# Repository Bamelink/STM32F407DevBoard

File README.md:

# STM32F407DevBoard
A developer board created in kicad featuring a STM32F407 MCU, LAN and CAN

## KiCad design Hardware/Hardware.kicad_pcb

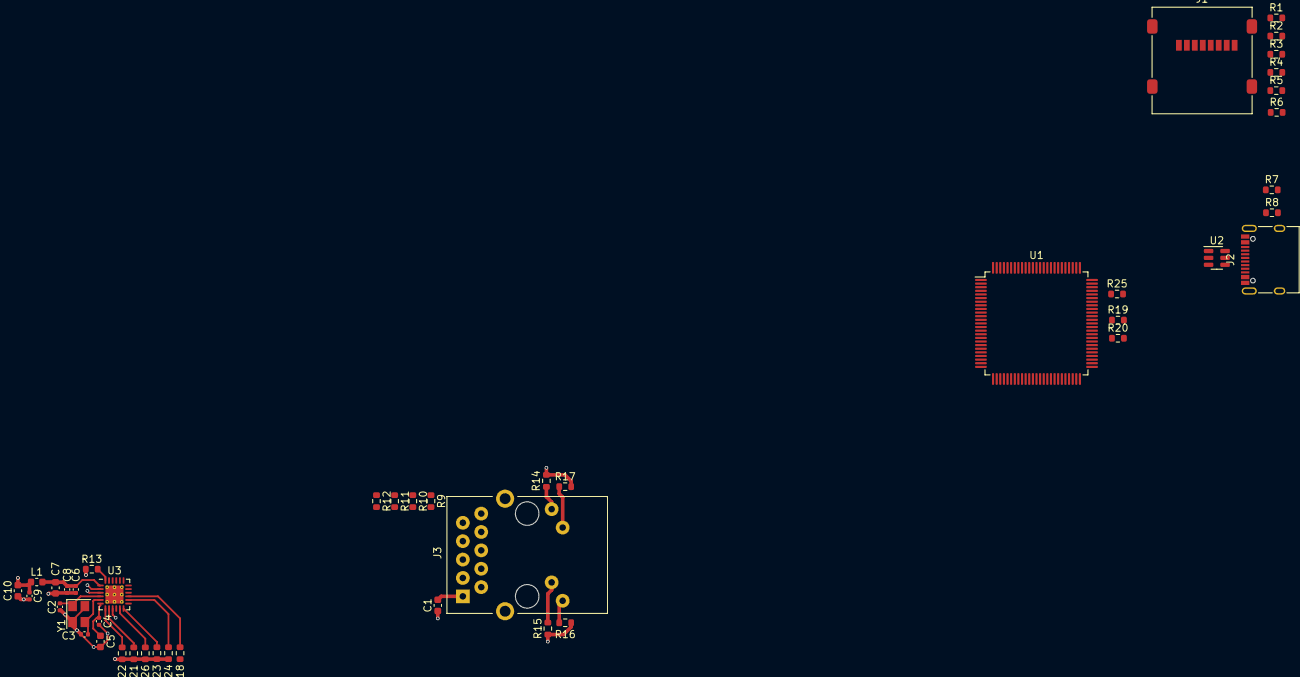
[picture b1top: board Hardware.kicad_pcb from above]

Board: 4 copper layers, 44 parts (0 on the bottom side), 41 nets.

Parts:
C1: TBD; C_0603_1608Metric
C2, C3: TBD; C_0402_1005Metric
C4: 470p; C_0402_1005Metric
C5: 1u; C_0603_1608Metric
C6, C8, C9: 100n; C_0402_1005Metric
C7, C10: 10u; C_0603_1608Metric
J1: Micro_SD_Card; microSD_HC_Molex_47219-2001
J2: USB_C_Receptacle_USB2.0; USB_C_Receptacle_XKB_U262-16XN-4BVC11
J3: RJ45_RB1-125B8G1A; RJ45_UDE_RB1-125B8G1A
L1: BLM18PG121SN1D; L_0603_1608Metric
R1, R2, R3, R4, R5, R6: 47k; R_0603_1608Metric
R7, R8: 5k1; R_0603_1608Metric
R9, R10, R11, R12: 50R; R_0603_1608Metric
R13: 12k1; R_0603_1608Metric
R14, R15: 10k; R_0603_1608Metric
R16, R17: 330R; R_0603_1608Metric
R18: 100k; R_0603_1608Metric
R19, R20, R25: 33R; R_0603_1608Metric
R21, R22, R24: 4k7; R_0603_1608Metric
R23, R26: 1k5; R_0603_1608Metric
U1: STM32F407VET6; LQFP-100_14x14mm_P0.5mm
U2: USBLC6-2SC6; SOT-23-6
U3: LAN8742A; VQFN-24-1EP_4x4mm_P0.5mm_EP2.5x2.5mm_ThermalVias
Y1: 25MHz; Crystal_SMD_3225-4Pin_3.2x2.5mm

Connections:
+3V3: C1.1, C9.1, C10.1, J1.4 (VDD), J3.R1 (CT), L1.2, R1.1, R2.1, R3.1, R4.1, R5.1, R6.1, R9.1, R10.1, R11.1, R12.1, R21.2, R22.1, R23.2, R24.1, R26.2, U1.6 (VBAT), U1.11 (VDD), U1.19 (VDD), U1.28 (VDD), U1.50 (VDD), U1.75 (VDD), U1.100 (VDD), U3.9 (VDDIO)
/IO/ETH_LED1: J3.L3, R15.1, U3.3 (LED1/REGOFF)
/IO/ETH_LED2: J3.L1, R14.1, U3.2 (LED2/~INTSEL)
/IO/ETH_RX+: J3.R4 (TD2+), R10.2, U3.23 (RXP)
/IO/ETH_RX-: J3.R5 (TD2-), R9.2, U3.22 (RXN)
/IO/ETH_TX+: J3.R2 (TD1+), R12.2, U3.21 (TXP)
/IO/ETH_TX-: J3.R3 (TD1-), R11.2, U3.20 (TXN)
/IO/SDIO_CK: J1.5 (CLK), R3.2, U1.80 (PC12)
/IO/SDIO_CMD: J1.3 (CMD), R4.2, U1.83 (PD2)
/IO/SDIO_D0: J1.7 (DAT0), R2.2, U1.65 (PC8)
/IO/SDIO_D1: J1.8 (DAT1), R1.2, U1.66 (PC9)
/IO/SDIO_D2: J1.1 (DAT2), R6.2, U1.78 (PC10)
/IO/SDIO_D3: J1.2 (DAT3/CD), R5.2, U1.79 (PC11)
/IO/USB_CC1: J2.A5 (CC1), R8.1
/IO/USB_CC2: J2.B5 (CC2), R7.1
/IO/USB_MCU_D+: U1.71 (PA12), U2.4 (I/O2)
/IO/USB_MCU_D-: U1.70 (PA11), U2.3 (I/O2)
ETH_CRS_DV: R19.2, R26.1, U3.11 (CRS_DV/MODE2)
ETH_MDC: U1.16 (PC1), U3.13 (MDC)
ETH_MDIO: R23.1, U1.25 (PA2), U3.12 (MDIO)
ETH_REF_CLK: R24.2, U1.24 (PA1), U3.14 (~INT/REFCLKO)
ETH_RST: R18.1, U1.15 (PC0), U3.15 (~RST)
ETH_RXD0: R21.1, R25.2, U3.8 (RXD0/MODE0)
ETH_RXD1: R20.1, R22.2, U3.7 (RXD1/MODE1)
ETH_TXD0: U1.51 (PB12), U3.17 (TXD0)
ETH_TXD1: U1.52 (PB13), U3.18 (TXD1)
ETH_TX_EN: U1.48 (PB11), U3.16 (TXEN)
GND: C1.2, C2.2, C3.2, C4.2, C5.2, C6.2, C7.2, C8.2, C9.2, C10.2, J1.6 (VSS), J1.9 (SHIELD), J2.A1 (GND), J2.A12 (GND), J2.B1 (GND), J2.B12 (GND), J3.R10 (GND), J3.SH, R7.2, R8.2, R13.2, R14.2, R15.2, R16.1, R17.1, R18.2, U1.10 (VSS), U1.20 (VSSA), U1.27 (VSS), U1.74 (VSS), U1.99 (VSS), U2.2 (GND), U3.25 (VSS), Y1.2, Y1.4
unnamed: J2.A6 (D+), J2.B6 (D+), U2.1 (I/O1)
unnamed: J2.A7 (D-), J2.B7 (D-), U2.6 (I/O1)
unnamed: J3.L2, R17.2
unnamed: J3.L4, R16.2
unnamed: R19.1, U1.32 (PA7)
unnamed: R25.1, U1.33 (PC4)
unnamed: R20.2, U1.34 (PC5)
unnamed: R13.1, U3.24 (RBIAS)
unnamed: C6.1, C7.1, C8.1, L1.1, U3.1 (VDD2A), U3.19 (VDD1A)
unnamed: C4.1, C5.1, U3.6 (VDDCR)
unnamed: C3.1, U3.5 (XTAL1/CLKIN), Y1.3
unnamed: C2.1, U3.4 (XTAL2), Y1.1
VBUS: J2.A4 (VBUS), J2.A9 (VBUS), J2.B4 (VBUS), J2.B9 (VBUS), U2.5 (VBUS)

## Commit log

2023-09-19 MCU with LAN and USB
2023-09-19 Add Layout constrains for JLC
2023-09-19 added stepfiles
